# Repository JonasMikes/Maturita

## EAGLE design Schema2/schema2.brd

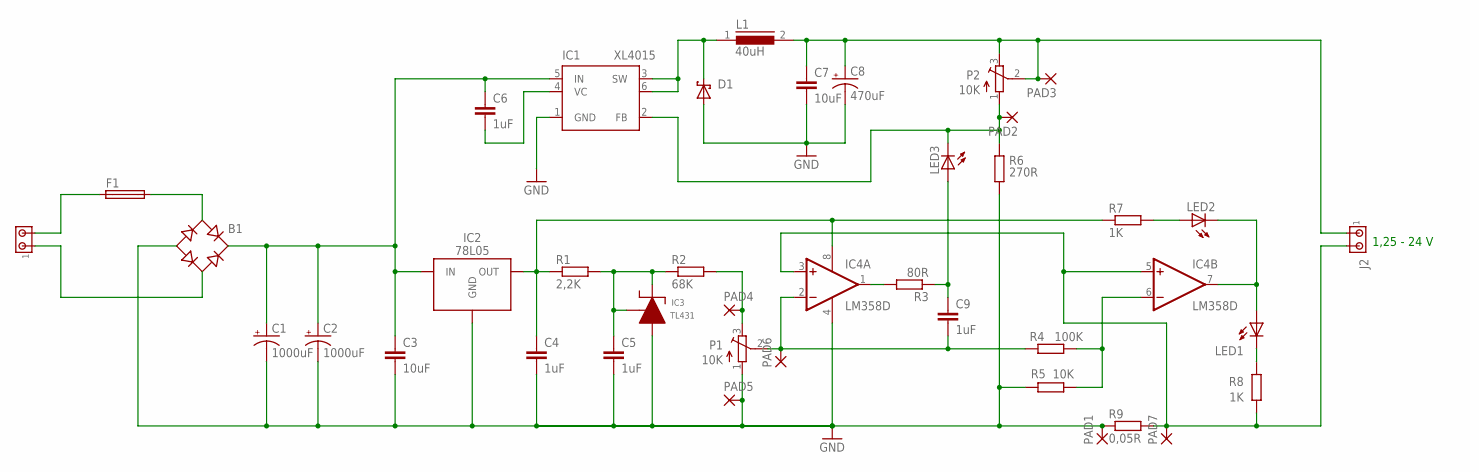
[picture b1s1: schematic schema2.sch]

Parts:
B1: RECTIFIER-2KBP; 2KBP
C1, C2: 1000uF; E5-10,5
C3, C7: 10uF; C0805
C4, C5, C6, C9: 1uF; C0805
C8: 470uF; 153CLV-0605
D1: SCHOTTKY-DIODE; DIODE_SMB
F1: FUSEGSH15; GSH15
IC1: XL4015; TO263-5
IC2: 78L05; SOT89
IC3: TL431; SOT-23
IC4: LM358D; SO08
J1, J2: MTA02-156; 1X2MTA
L1: 40uH; ED16
LED1, LED2, LED3: LED_E; LED_1206
P1, P2: 10K; 3223G
PAD1, PAD2, PAD3, PAD4, PAD5, PAD6, PAD7: 2,15/1,0
R1: 2,2K; M0805
R2: 68K; M0805
R3: 80R; M0805
R4: 100K; M0805
R5: 10K; M0805
R6: 270R; M0805
R7, R8: 1K; M0805
R9: 0,05R; R2512

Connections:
GND: B1.-, C1.-, C2.-, C3.2, C4.2, C5.2, C7.2, C8.-, D1.A (C), IC1.1 (GND), IC2.2 (GND), IC2.2@1 (GND), IC3.3 (ANODE), IC4.4 (V-), P1.1 (A), PAD1.1, PAD5.1, R5.2, R6.1, R9.1
unnamed: F1.1, J1.1 (2)
unnamed: B1.AC1, F1.2
unnamed: B1.AC2, J1.2 (1)
unnamed: IC4.1 (OUT), R3.2
unnamed: C6.2, IC1.4 (VC)
unnamed: P1.3 (E), PAD4.1, R2.2
unnamed: C9.2, IC4.2 (-IN), P1.2 (S), PAD6.1, R4.2
unnamed: D1.C (A), IC1.3 (SW), IC1.6 (SW), L1.1
unnamed: C9.1, LED3.A, R3.1
unnamed: C7.1, C8.+, J2.2 (1), L1.2, P2.2 (S), P2.3 (E), PAD3.1
unnamed: IC1.2 (FB), LED3.C, P2.1 (A), PAD2.1, R6.2
unnamed: C5.1, IC3.1 (CATHODE), IC3.2 (REF), R1.2, R2.1
unnamed: IC4.6 (-IN), R4.1, R5.1
unnamed: LED1.C, R8.2
unnamed: IC4.7 (OUT), LED1.A, LED2.C
unnamed: LED2.A, R7.2
unnamed: IC4.3 (+IN), IC4.5 (+IN), J2.1 (2), PAD7.1, R8.1, R9.2
VCC_IN: B1.+, C1.+, C2.+, C3.1, C6.1, IC1.5 (IN), IC2.3 (IN)
VNN: C4.1, IC2.1 (OUT), IC4.8 (V+), R1.1, R7.1

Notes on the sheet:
1,25 - 24 V

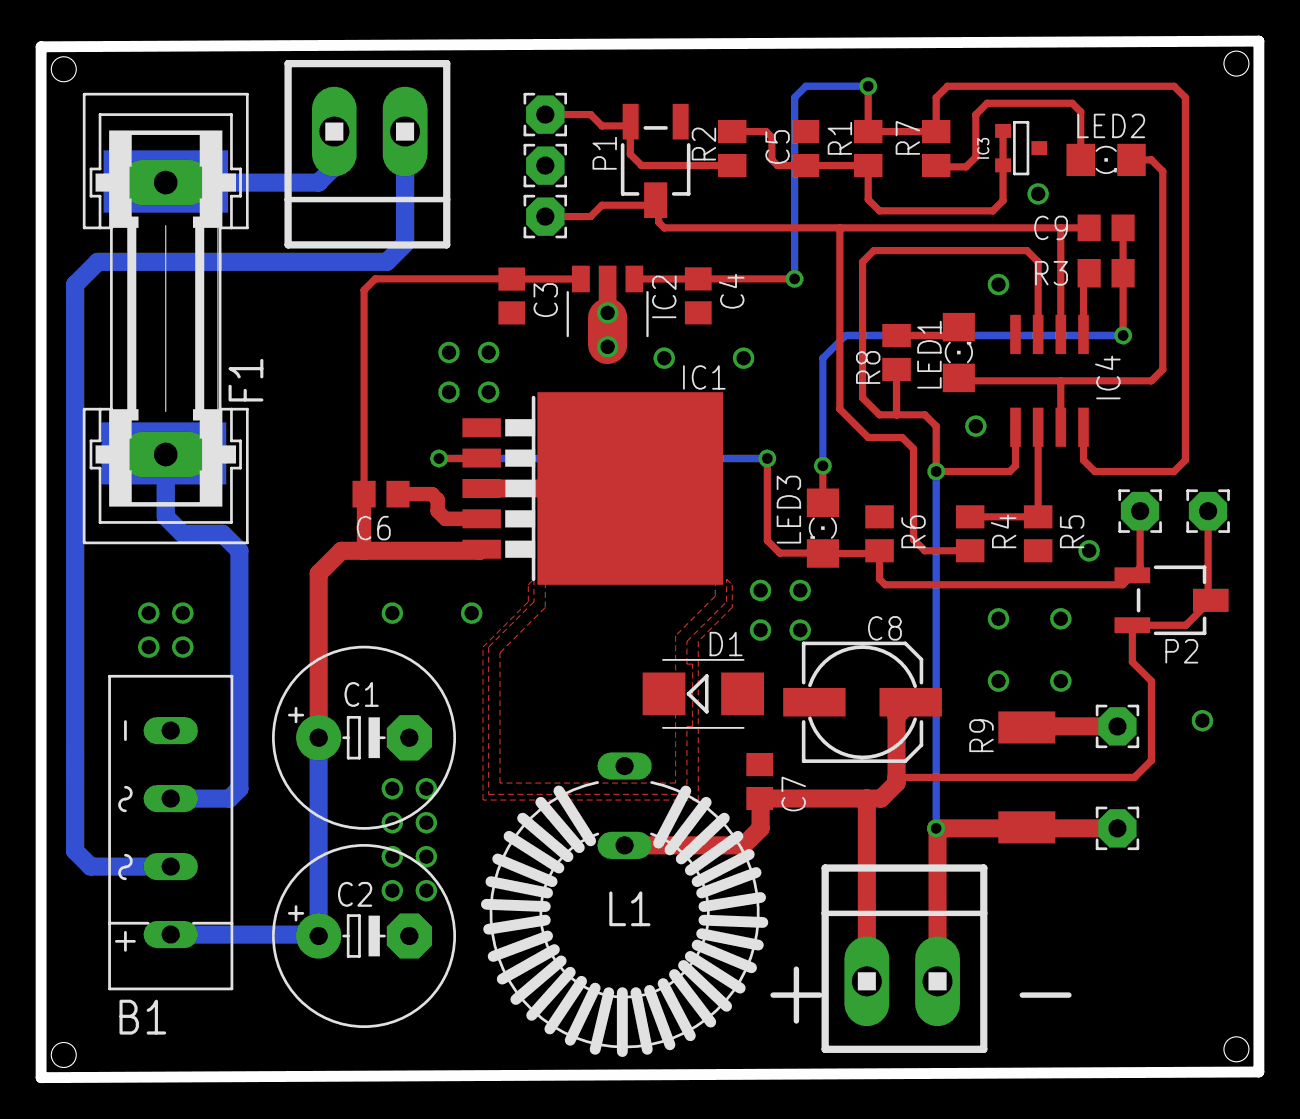
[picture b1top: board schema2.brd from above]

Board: 2 copper layers, 68.2 x 58.1 mm, 40 parts (0 on the bottom side), 20 nets.

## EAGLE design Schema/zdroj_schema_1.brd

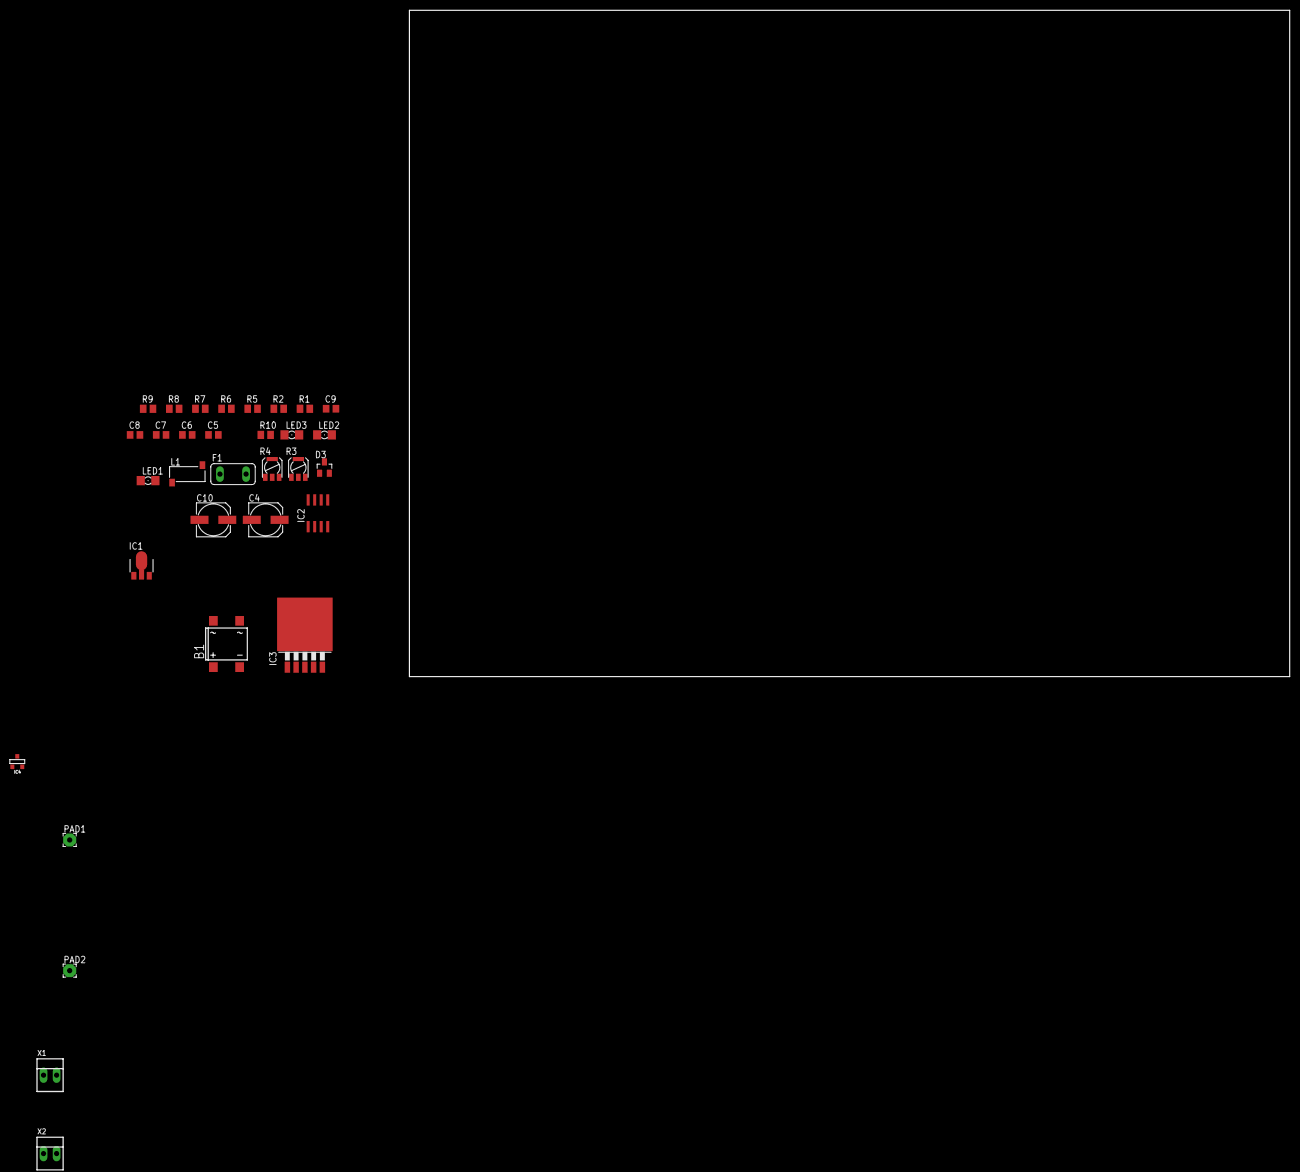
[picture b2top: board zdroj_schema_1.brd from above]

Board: 2 copper layers, 171.1 x 129.5 mm, 32 parts (0 on the bottom side), 19 nets, no tracks yet.

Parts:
B1: DBS104G; DBS
C4, C10: 153CLV-0605
C5, C6, C7, C8, C9: C0805
D3: BAT54; SOT23
F1: TE5
IC1: 78L05F; SOT89
IC2: LM358D; SO08
IC3: LM2596S; TO263-5
IC4: TL431ACDBZ; SOT-23
L1: SM-L15B
LED1, LED2, LED3: LED_1206
PAD1, PAD2: 2,54/1,0
R1, R2, R5, R6, R7, R8, R9, R10: M0805
R3, R4: PC25
X1, X2: 22-23-2021

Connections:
GND: B1.-, C4.-, C5.2, C6.2, C7.2, C9.2, C10.-, D3.1, IC1.2, IC2.4, IC3.3, IC4.3, PAD2.1, R4.A, R5.1, R7.2, R8.2
unnamed: F1.2, X1.2
unnamed: B1.AC1, F1.1
unnamed: B1.AC2, X1.1
unnamed: C8.1, IC2.1, LED1.A
unnamed: B1.+, C4.+, C5.1, IC1.3, IC3.1
unnamed: C6.1, IC1.1, IC2.8, R1.1, R9.2
unnamed: D3.3, IC3.2, L1.1
unnamed: C7.1, IC4.1, IC4.2, R1.2, R2.1
unnamed: R2.2, R4.E
unnamed: C8.2, IC2.2, R4.S, R6.2
unnamed: C9.1, C10.+, L1.2, R3.E, R3.S, X2.1
unnamed: IC2.6, R6.1, R7.1
unnamed: LED2.A, R9.1
unnamed: IC2.7, LED2.C, LED3.A
unnamed: LED3.C, R10.1
unnamed: IC3.4, LED1.C, R3.A, R5.2
unnamed: IC2.3, IC2.5, R8.1, R10.2, X2.2
unnamed: IC3.5, PAD1.1

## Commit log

2023-09-21 Pridal jsem soubor pro zadani maturitni prace
2023-09-21 Pridani parametru zdroje
2023-09-21 Změna readme
2023-09-21 Uprava readme
2023-09-21 pridani souboru s vykazem praxe
2023-10-05 přidání referencí
2023-10-05 update zadaní
2023-10-11 přidání dokumentace
2023-10-12 přidání seznamu součástek
2023-10-12 přidání souboru se schema
2023-11-01 update schema
2023-11-09 update dokumentace
2023-11-09 update referencí
2023-11-16 aktualizace práce
2023-11-16 nahrání obrázků
2023-12-06 update dokumentace a obrázků
2023-12-14 update práce a obrázků
2024-01-04 druhá verze DPS
2024-01-11 přidání měření
2024-02-08 krabicka spodni dil
2024-02-15 update obrázků
2024-02-15 pouzdro zdroje
